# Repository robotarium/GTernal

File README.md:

# Setup Process for GTernal

# 1 - Repository Setup
During the setup process, each robot runs an automatic setup script which clones the firmware from a GitHub repository. By default, the setup script clones the official GTernal repository. This needs to be changed to clone your repository with updated configuration files. If you are not familiar with Git or GitHub, please refer to here: https://docs.github.com/en/get-started/quickstart/fork-a-repo

1. Fork this GTernal repository.
2. Clone the forked repository to your computer.
3. Update 'GTernal/config/env_variables.sh'
4. Push the change to your repository.

# 2 - Program Teensy
1. Install Teensyduino (https://www.pjrc.com/teensy/td_download.html)
2. Copy and paste all library folders in `GTernal/firmware/Teensy/libraries` to `Arduino/libraries`.
> [!NOTE]
> The absolute path for the `Arduino/libraries` directory is OS dependent, and this can be found here: https://support.arduino.cc/hc/en-us/articles/4412950938514-Open-the-Sketchbook
    
> [!NOTE]
> The firmware for Teensy requires ArduinoJson 5.13 which is included in `GTernal/firmware/Teensy/libraries`.
> ArduinoJson 6 is currently not compatible with the firmware.
3. Connect a Teensy to the computer using a micro-USB cable.
> [!NOTE]
> The micro-USB cable needs to be directly connected to the Teensy and not the micro-USB port on the robot PCB.
4. Run Teensyduino and open `defaultOperation.ino` located in `GTernal/firmware/defaultOperation` directory.
5. Select the Teensy board to be flashed under `Tools > Port`
6. Click the upload icon (right arrow icon).

# 3 - Make the Base Image for Raspberry Pi
## 1 - Install Raspberry Pi OS on an SD Card
1. Install and run the Raspberry Pi Imager (https://www.raspberrypi.com/software/). The instuction is for Raspberry Pi Imager v.1.8.5
2. For 'Raspberry Pi Device,' select the version of the Pi used.
3. For 'Operating System,' select `Raspberry Pi OS (other)` and select `Raspberry Pi OS (Legacy, 64-bit) Lite`. For Raspberry Pi Zero 1s, select `Raspberry Pi OS (Legacy, 32-bit) Lite`.
4. For 'Storage,' choose the micro-SD card to be used.
5. Click 'NEXT' and 'EDIT SETTINGS.'
6. Under 'GENERAL' tab, check 'Set username and password' and type `pi` for the 'Username' and `raspberry` for 'Password.'
7. Next, check 'Configure wireless LAN' and enter 'SSID' and 'Password' for the router.
8. Change 'Wireless LAN country' to 'US.' 'Set locale settings' is optional.
9. Under 'SERVICES' tab, check 'Enable SSH' and 'Use password authentication'
10. Click 'SAVE' and click 'YES.'
> [!NOTE]
> Whenever the Raspberry Pi Imager is restarted, make sure to re-type the passwords for the Pi and the Wifi. The Raspberry Pi Imager seems to be ruining the passwords saved in the advanced setting when the program is restarted even if the 'Image customization options' is set to 'to always use.'

## 2 - Setup the Base Image
1. Insert the SD card from the previous step into a Raspberry Pi and power it on. It should automatically connect to the wifi specified in Step 2.1.7. The Pi needs some time to boot for the first time.
2. Identify the MAC address of the Raspberry Pi. On a Linux comptuer, this can be done by running
    ```
    sudo arp-scan -I <network-device-name> -l -t 100 -r 5
    ```
    Alternatively, you can navigate to the router settings page (typically '192.168.1.1' or '10.0.0.1') using a web browser. The new Pi will appear as 'RASPBERRYPI.'
3. Add the MAC address to 'path-to-parent-directory/GTernal/config/mac_list.json' file as
    ```
    "<MAC-address-of-Pi>":"base_image"
    ```
    e.g., `{
            "d8:3a:dd:bc:0c:3c":"base_image"
           }`
4. On your computer, run
    ```
    cd <path-to-parent-directory>/GTernal/interfacing
    ./setup.sh setup_base_image
    ```
    When prompted for password, enter the password of your computer. When prompted 'Enter secrets for robots,' enter the password for the Raspberry Pis, `raspberry`.
    This will automatically setup the SD card as the base image. Wait for 'DONE SETTING UP BASE IMAGE' message on the terminal.
5. In case of using another network for the robot for actual deployment, edit the wireless LAN credentials.
    First, ssh into the robot.
    ```
    ssh pi@<ip-address-of-robot>
    ```
    Then, edit the wpa_supplicant.conf file to update the wireless LAN credentials.
    ```
    sudo nano /etc/wpa_supplicant/wpa_supplicant.conf
    ```

6. (Optional) Pull the base firmware image to reduce the setup time.
    - If the wireless LAN credential has changed in the previous step, restart the Raspberry Pi.<br>
        ```
         ssh pi@<ip-address-of-robot>
         sudo reboot
        ```
    - Follow the instructions in Section 4 up to 4.1.2.<br>
    - Next, ssh into the robot.
        ```
        ssh pi@<ip-address-of-robot>
        ```
    - Run
        ```
        cd <path-to-parent-directory>/GTernal/docker/base_image/
        ./docker_pull.sh
        ```

5. On the ssh terminal, shutdown the Pi by running
    ```
    sudo reboot
    ```
6. Remove the SD card from the Pi and insert it to your computer.
7. On your computer, identify the name of the SD card by running
    ```
    sudo fdisk -l
    ```
    The device name will be something like '/dev/sdb'. Look for the device with the storage size that matches the capacity of the SD card.
> [!NOTE]
> You must enter the device name without any numbers. For example, if you see '/dev/sdb1' and '/dev/sdb2', the device name is `/dev/sdb`.
8. Create the image of the SD card on your computer by running
    ```
    sudo dd if=<name-of-the-sd-card> of=<desired-directory>/GTernal_base_image.img bs=4M status=progress
    ```
    e.g., `sudo dd if=/dev/sdb of=~/GTernal_base_image.img bs=4M status=progress`<br>
9. Shrink the size of the base image by running
    ```
    wget https://raw.githubusercontent.com/Drewsif/PiShrink/master/pishrink.sh

    chmod +x ./pishrink.sh

    sudo ./pishrink.sh <path-to-the-base-image>/GTernal_base_image.img
    ```
    e.g., `sudo ./pishrink.sh ~/GTernal_base_image.img`

## 3 - Clone the Base Image
1. Insert a new SD card into your computer to load the base image.
2. Identify the name of the SD card by running
    ```
    sudo fdisk -l
    ```
3. Run
    ```
    sudo mount | grep <device-name>
    ```
    e.g. `sudo mount | grep /dev/sdb`
    to check if any of the partitions of the SD card is mounted.<br>
    If the output is not blank, run
    ```
    sudo umount <device-name1> <device-name2> ... <device-nameN>
    ```
    e.g. `sudo umount /dev/sdb1 /dev/sdb2`<br>
    to unmount all listed partitions of the device.
4. Load the SD card with the base image by running
    ```
    sudo dd if=<path-to-the-base-image>/GTernal_base_image.img of=<name-of-the-sd-card> status=progress
    ```
    e.g., `sudo dd if=~/GTernal_base_image.img of=/dev/sdb bs=4M status=progress`<br>
> [!NOTE]
> The status message may stop updating at some point. Please continue waiting for the write process to finish.
5. Load as many SD cards as needed with the base image. More detailed instructions on cloning an SD card image can be found here: https://beebom.com/how-clone-raspberry-pi-sd-card-windows-linux-macos/

# 4 - Load the Raspberry Pi with the Default firmware
This section assumes that:
1. You have micro-SD cards loaded as detailed in the previous section.
2. You have fully assembled robots.
> [!NOTE]
> Check if the Pi and Teensy are connected through UART. If the Pi is not connected with a programmed Teensy as instructed in Step 1, the firmware will not be started by the setup script properly in the following steps.
3. Only the new robots to be setup are connected to the WiFi.
> [!WARNING]
> The current automatic setup script looks for all robots with the MAC addresses specified in 'GTernal/config/mac_list.json' file and starts the setup process for the robots. Therefore, it will start the setup process even for the robots already with the firmware installed if they are connected to the WiFi. Since this may cause problems for the existing robots, it is advised to only turn on the new robots to be set up.

## 1 - Firmware Docker Image Setup
The "docker_run.sh" script makes each robot pull the firmware image from either Docker Hub of a local Docker registry instead of building the firmware docker image directly on each robot. This saves a lot of time when building multiple robots. Also, with "v2tec/watchtower" image running on the robots, each robot downloads and runs the newest firmware image uploaded to the Docker Hub automatically. Therefore, it is unnecessary to manually update the firmware of each robot when a new firmware image is built and pushed to Docker Hub/local Docker registry.

### 1 - Build the Base Firmware Image
1. Inspect and update the environment variables in `config/env_variables.sh`
2. Build the base image
    ```
    cd <path-to-parent-directory>/GTernal/docker/base_image/
    ./docker_build.sh
    ```

### 2 - Tag the Base Image and Push it to a Docker Registry

#### 2.1 - Docker Hub (Online)
1. Log into the Docker Hub with
    ```
    docker login
    ```
2. Run
    ```
    cd <path-to-parent-directory>/GTernal/docker/base_image/
    ./docker_push.sh
    ```

#### 2.2 - Local Docker registry (Local)
1. Start a local Docker registry
    ```
    cd <path-to-parent-directory>/GTernal/docker/
    ./docker_registry.sh
    ```
2. Run
    ```
    cd <path-to-parent-directory>/GTernal/docker/base_image/
    ./docker_push_local.sh
    ```

### 3 - Build the Firmware Image
1. Build the firmware image
    ```
    cd <path-to-parent-directory>/GTernal/docker/
    ./docker_build.sh
    ```

### 4 - Tag the Firmware Image and Push it to a Docker Registry

#### 4.1 - Docker Hub (Online)
1. Run
    ```
    cd <path-to-parent-directory>/GTernal/docker/
    ./docker_push.sh
    ```

#### 4.2 - Local Docker registry (Local)
1. Run
    ```
    cd <path-to-parent-directory>/GTernal/docker/
    ./docker_push_local.sh
    ```

## 2 - Robot Setup
<!-- > [!IMPORTANT]
> It is recommended to only turn on the new robots to be set up. The current automatic setup script looks for all robots with the MAC addresses specified in 'GTernal/config/mac_list.json' file and starts the setup process for the robots. Therefore, it will start the setup process even for the robots already with the firmware installed if they are connected to the WiFi. Since this may cause problems for the existing robots, it is recommended to only turn on the new robots that need to be set up. -->
1. Insert the loaded micro-SD cards to the robots' Raspberry Pis and power the robots up using the switch on each PCB. They should automatically connect to the wifi specified in Step 3.7.

2. On your computer, check if all the Raspberry Pis are connected to the WiFi router by running
    ```
    sudo arp-scan -I <network-device-name> -l -t 100 -r 5
    ```
    e.g., `sudo arp-scan -I enp4s0 -l -t 100 -r 5`

    Check if the number of Raspberry Pis found by the above command matches the total number of Raspberry Pis being set up. Wait a few more minutes and check again if not all Pis show up in the list.

> [!NOTE]
> The \<network-device-name\> can be found by running 'ifconfig' command into the terminal. There may be multiple network devices on your computer. The right device is the one connected to the same WiFi network as the Raspberry Pis. Typically, the local IP address assigned by a network router is '192.168.x.x' or '10.0.x.x.'

3. Assign an unallocated robot ID# for the MAC address of a Raspberry Pi found in the previous step. Then, add/replace the robot ID# and the MAC address of the Raspberry Pi in 'GTernal/config/mac_list.json'

> [!NOTE]
> When assigning an index to a new robot, assign an Aruco tag ID or the ID engraved on a Vicon hat plate. Make sure not to use any numbers that are already assigned to other robots. The lasercutting design files for the Vicon hats can be found in `GTernal/GTernal_design_files`

<!-- 4. Replace lines 12 and 13 in 'GTernal/docker/docker_run.sh' with the IP address and port of the MQTT host.

   > [!NOTE]
   > The default GTernal firmware requires an MQTT broker. For more information about the MQTT broker, please refer to https://github.com/robotarium/mqtt_broker. -->

4. Start the setup process by running
    ```
    cd path-to-parent-directory/GTernal/interfacing
    ./setup.sh setup_from_base <#-of-robots-being-set-up>
    ```
    e.g., `./setup.sh setup_from_base 10`

    When prompted 'Enter secrets for robots,' enter the password for the Raspberry Pis, 'raspberry'

> [!NOTE]
> The config/mac_list.json file of the robots will be updated to the config/mac_list.json file on your computer via SCP.

<!-- 5. Update the 'mac_list.json' file on the robots by running
```
cd path-to-parent-directory/GTernal/interfacing
./update_mac.sh <#-of-robots-being-set-up>
```
e.g. ./update_mac.sh 10

When prompted 'Enter secrets for robots,' enter the password for the Raspberry Pis, 'raspberry'

The Raspberry Pis will reboot after updating 'mac_list.json' file. -->

<!-- ## 2 - Network Host Name Change (Optional)
This process changes the name of the Raspberry Pi on the network. This helps to identify each robot easily on the router page ('192.168.1.1' or '10.0.0.1'). See Step 2.2, if you forgot how to access the router page.

After the setup process is completed,
Run
```
sudo raspi-config nonint do_hostname <hostname>
```
on the Raspberry Pi, and change the Host Name to 'robot#' where # is the new robot index assigned to the Pi in Step 3.

Reboot the Pi to apply the new network host name by selecting 'yes' when the raspi-config asks for a restart, or by using
```
sudo reboot
``` -->

<!-- ## 2 - Manual Installation

This section details the manual installation process for the firmware. This process is unnecessary if the automatic setup in the previous section is performed.

### 1 Remove Unused Services

Remove plymouth with 

```
sudo apt-get purge --remove plymouth
```

Disable unused services with 

```
sudo systemctl disable triggerhappy.service
sudo systemctl disable hciuart.service
sudo systemctl disable keyboard-setup.service
sudo systemctl disable dphys-swapfile.service
```

### 2 - Install Docker

This section follows from the official (Docker)[https://docs.docker.com/install/linux/docker-ce/ubuntu/].  First, remove old versions of Docker.

```
sudo apt-get remove docker docker-engine docker.io
```

Next, install Docker using the convenience script.

```
curl -fsSL get.docker.com -o get-docker.sh && export VERSION=23.0 && sh get-docker.sh
```

Now tie Docker to the pi user so that we don't need sudo to use Docker.

```
sudo usermod -aG docker pi
```

### 3 - Clone Git Repos and install Deps

Install pip for python3

```
sudo apt-get install python3-pip
```

To clone the firmware, run
```
sudo apt-get install git
git clone https://github.com/robotarium/gritsbot_2
```

Also, install the MAC discovery repository
```
git clone https://github.com/robotarium/mac_discovery
```

as well as the python serial library used to communicate to the robot.

```
python3 -m pip install pyserial
```

### 4 - WiFi Power Management

Turn off power management by adding the line
```
/sbin/iw dev wlan0 set power_save off
```

in the file /etc/rc.local.  This line disables WiFi power management on boot.

### 5 - Start necessary containers

From wherever the git repository is cloned, run 
```
cd <path_to_gritsbot_2_repo>/docker
./docker_run.sh
./docker_watch.sh
```
which will permanently start a Docker container running the firmware and the watchtower container.  Watchtower watches containers and automatically updates them from Dockerhub.  This watchtower instance
checks and updates **all running containers**, so this instance will also update the MAC container as well.

Start MAC discovery as well with
```
cd <path_to_mac_discovery_repo>/docker
./docker_run.sh
``` -->

# 5 - Test Robots
1. Clone the mqtt_broker repo
    ```
    git clone https://github.com/robotarium/mqtt_broker.git
    ```
2. Run the MQTT broker Docker container
    ```
    cd <path-to-parent-directory>/mqtt_broker/docker/
    ./docker_run.sh <ip-address-of-your-computer>
    ```
3. Clone the vizier repository with
    ```
    git clone https://github.com/robotarium/vizier.git
    ```

4. Install vizier with
    ```
    cd path-to-parent-directory/vizier
    python3 -m pip install .
    ```

5. Check the status of a robot with
    ```
    python3 -m vizier.vizier --host <ip-address-of-MQTT-host> --get <robot#>/status
    ```
    e.g., `python3 -m vizier.vizier --host 192.168.1.8 --get 21/status`

6. Send a motor command to a robot with
    ```
    python3 -m vizier.vizier --host <ip-address-of-MQTT-host> --publish matlab_api/<robot#> '{"v":1.0,"w":0.0}'
    ```
    e.g., `python3 -m vizier.vizier --host 192.168.1.8 --publish matlab_api/21 '{"v":1.0,"w":0.0}'`

    "v" and "w" are the desired linear and angular velocity of the robot, respectively. With this command, the robot will stop after 1 second for safety purposes.

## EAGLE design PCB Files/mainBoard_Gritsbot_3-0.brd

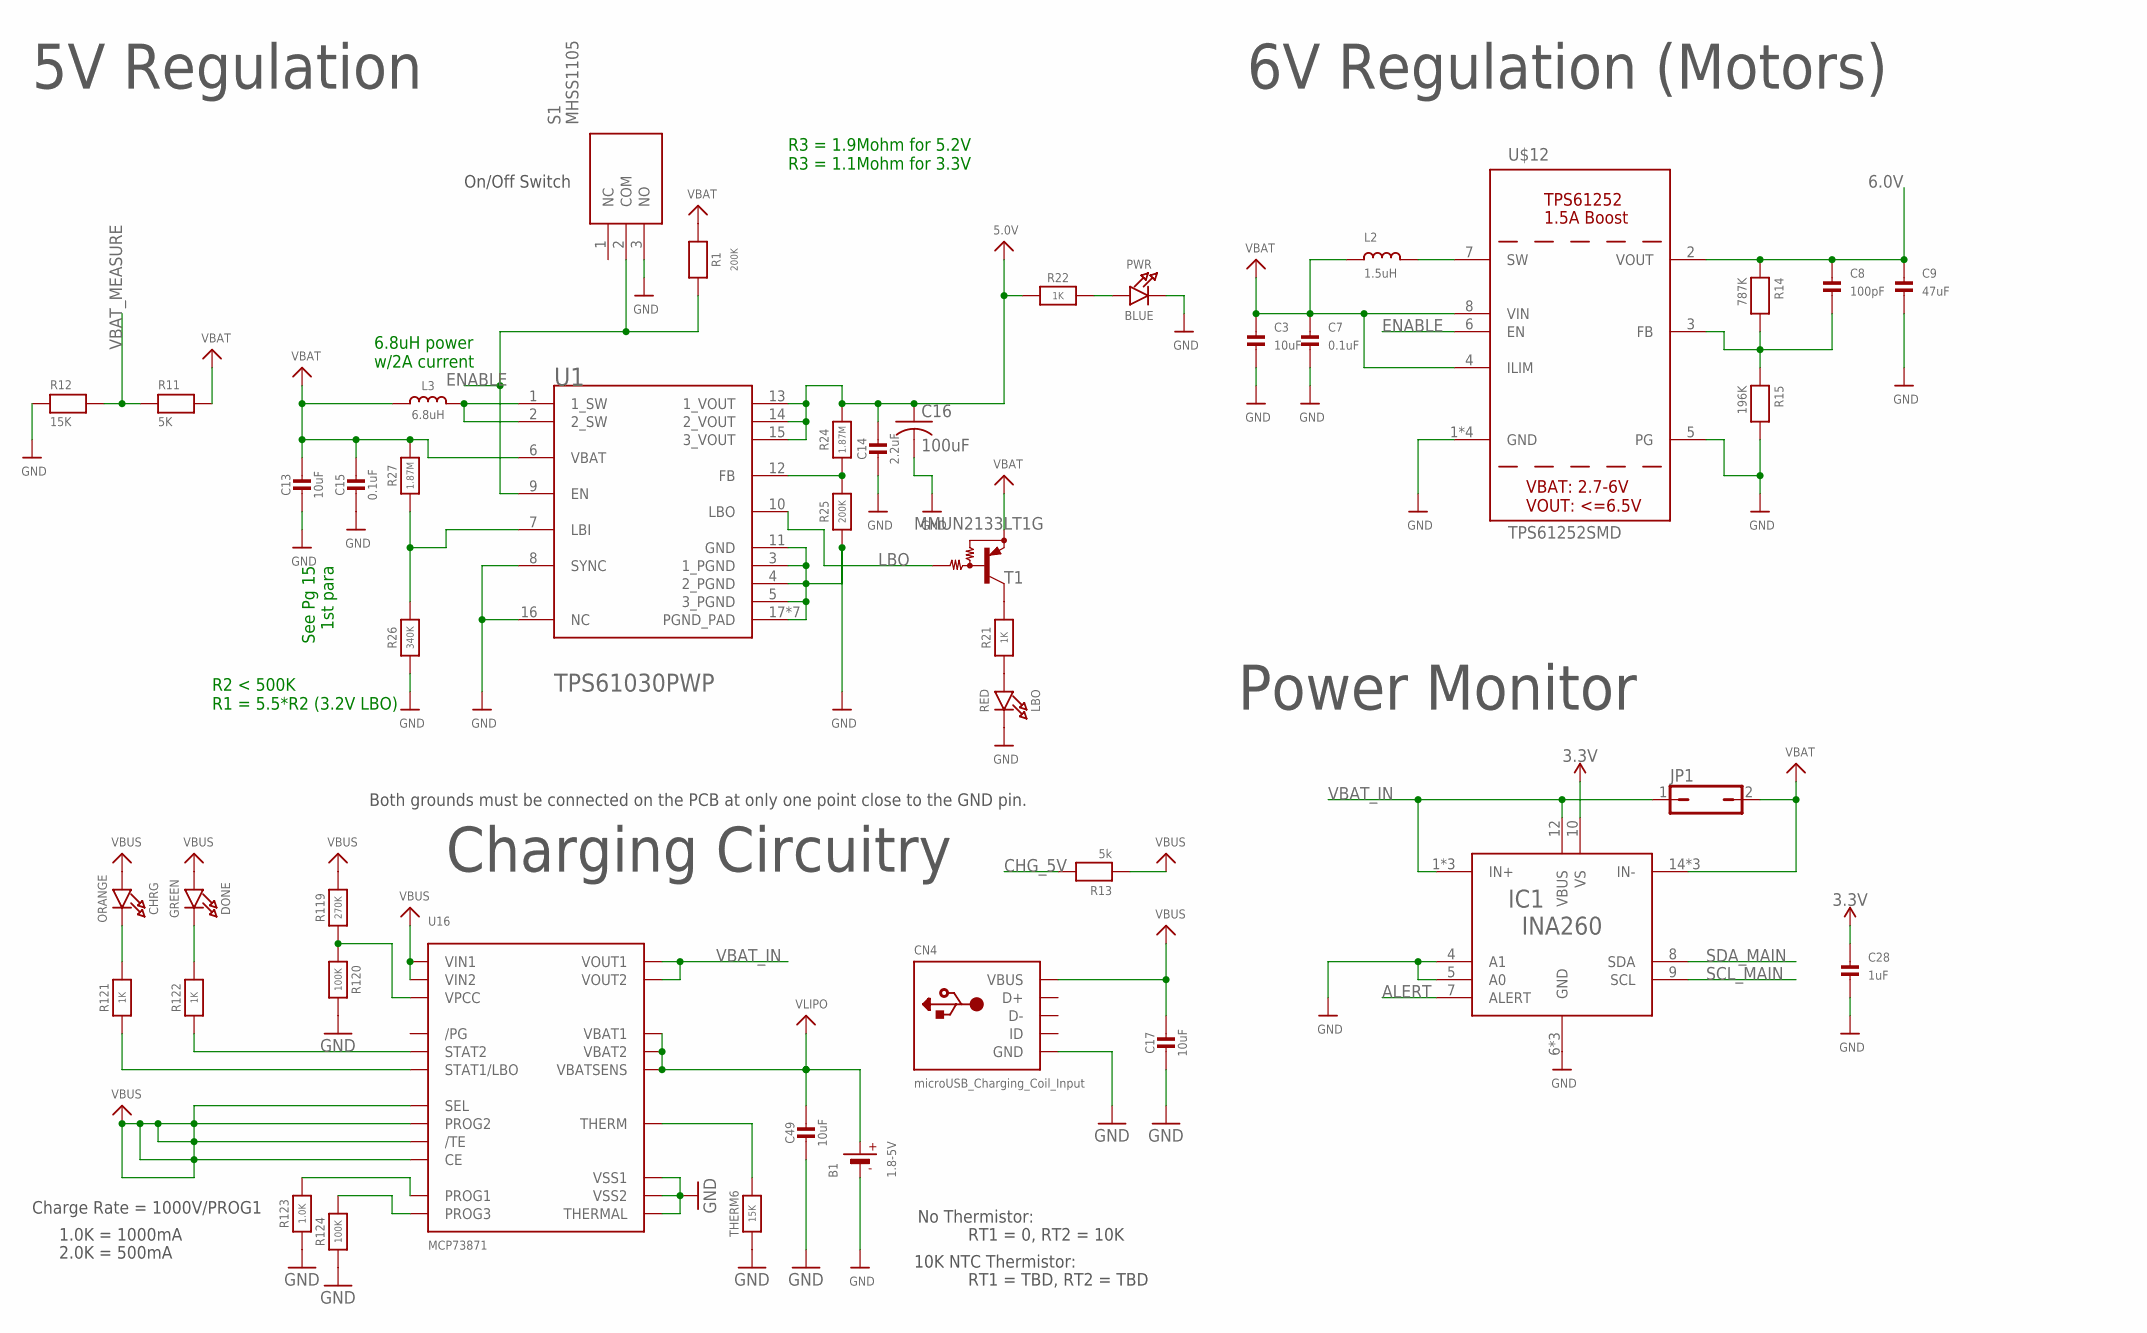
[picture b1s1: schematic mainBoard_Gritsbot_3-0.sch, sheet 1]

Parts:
B1: 1.8-5V; JSTPH2
C3: 10uF; 0603
C7: 0.1uF; 0805
C8: 100pF; 0603
C9: 47uF; 1206
C13, C17, C49: 10uF; 0805-NO
C14: 2.2uF; 0805-NO
C15: 0.1uF; 0805_10MGAP
C16: 100uF; C1210
C28: 1uF; 0603-NO
CHRG: ORANGE; CHIPLED_0805_NOOUTLINE
CN4: microUSB_Charging_Coil_Input; 4UCONN_20329
DONE: GREEN; CHIPLED_0805_NOOUTLINE
IC1: INA260; TSSOP16
JP1: JP1Q; JP1
L2: 1.5uH; MURATA_DFE252012P-1R5M=P2
L3: 6.8uH; INDUCTOR_5X5MM_TDK_VLC5045
LBO: RED; CHIPLED_0805_NOOUTLINE
PWR: BLUE; CHIPLED_0805_NOOUTLINE
R1, R25: 200K; 0805-NO
R11: 5K; 0805
R12: 15K; 0805
R13: 5k; 0805
R14: 787K; 0805
R15: 196K; 0805
R21, R22, R121, R122: 1K; 0805-NO
R24: 1.87M; 0805-NO
R26: 340K; _0805MP
R27: 1.87M; _0805MP
R119: 270K; 0805-NO
R120, R124: 100K; 0805-NO
R123: 1.0K; 0805-NO
S1: MHSS1105
T1: MMUN2133LT1G; SC59-BEC
THERM6: 15K; 0805-NO
U1: TEXAS_INSTRUMENTS_TPS61030PWPTEXAS_INSTRUMENTS_TP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; TEXAS_INSTRUMENTS_TPS61030PWP_0
U16: MCP73871; QFN20_4MM
U$12: TPS61252SMD; TPS61252

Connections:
3.3V: C28.1, IC1.10 (VS); also elsewhere on the board
5.0V: C14.1, C16.1, R22.1, R24.2, U1.13 (1_VOUT), U1.14 (2_VOUT), U1.15 (3_VOUT); also elsewhere on the board
6.0V: C8.1, C9.1, R14.1, U$12.2 (VOUT); also elsewhere on the board
ALERT: IC1.7 (ALERT)
CHG_5V: R13.2; also elsewhere on the board
ENABLE: R1.2, S1.2 (COM), U1.9 (EN), U$12.6 (EN)
GND: B1.1 (-), C3.2, C7.2, C9.2, C13.2, C14.2, C15.2, C16.2, C17.2, C28.2, C49.2, CN4.BASE@1 (GND), CN4.BASE@2 (GND), CN4.GND, CN4.SPRT@1 (GND), CN4.SPRT@2 (GND), CN4.SPRT@3 (GND), CN4.SPRT@4 (GND), IC1.4 (A1), IC1.5 (A0), IC1.6 (GND), IC1.11 (GND), IC1.13 (GND), LBO.C, PWR.C, R12.1, R15.2, R25.1, R26.1, R120.2, R123.1, R124.1, S1.3 (NO), THERM6.1, U1.3 (1_PGND), U1.4 (2_PGND), U1.5 (3_PGND), U1.8 (SYNC), U1.11 (GND), U1.16 (NC), U1.17 (PGND_PAD), U1.PAD_1 (PGND_PAD), U1.PAD_2 (PGND_PAD), U1.PAD_3 (PGND_PAD), U1.PAD_4 (PGND_PAD), U1.PAD_5 (PGND_PAD), U1.PAD_6 (PGND_PAD), U16.P$10 (VSS1), U16.P$11 (VSS2), U16.P$21 (THERMAL), U$12.1 (GND), U$12.5 (PG), U$12.P$2_GND (GND), U$12.P$3_GND (GND), U$12.THERMAL_GND (GND); also elsewhere on the board
LBO: T1.B, U1.10 (LBO)
unnamed: R24.1, R25.2, U1.12 (FB)
unnamed: L2.P$2 (2), U$12.7 (SW)
unnamed: C8.2, R14.2, R15.1, U$12.3 (FB)
unnamed: L3.P$2 (2), U1.1 (1_SW), U1.2 (2_SW)
unnamed: R26.2, R27.1, U1.7 (LBI)
unnamed: LBO.A, R21.1
unnamed: R21.2, T1.C
unnamed: PWR.A, R22.2
unnamed: R119.1, R120.1, U16.P$2 (VPCC)
unnamed: R122.1, U16.P$7 (STAT2)
unnamed: R121.1, U16.P$8 (STAT1/LBO)
unnamed: R123.2, U16.P$13 (PROG1)
unnamed: THERM6.2, U16.P$5 (THERM)
unnamed: DONE.C, R122.2
unnamed: CHRG.C, R121.2
unnamed: R124.2, U16.P$12 (PROG3)
SCL_MAIN: IC1.9 (SCL); also elsewhere on the board
SDA_MAIN: IC1.8 (SDA); also elsewhere on the board
VBAT: C3.1, C7.1, C13.1, C15.1, IC1.14 (IN-), IC1.15 (IN-), IC1.16 (IN-), JP1.2, L2.P$1 (1), L3.P$1 (1), R1.1, R11.2, R27.2, T1.E, U1.6 (VBAT), U$12.4 (ILIM), U$12.8 (VIN)
VBAT_IN: IC1.1 (IN+), IC1.2 (IN+), IC1.3 (IN+), IC1.12 (VBUS), JP1.1, U16.P$1 (VOUT1), U16.P$20 (VOUT2)
VBAT_MEASURE: R11.1, R12.2; also elsewhere on the board
VBUS: C17.1, CHRG.A, CN4.VBUS, DONE.A, R13.1, R119.2, U16.P$3 (SEL), U16.P$4 (PROG2), U16.P$9 (/TE), U16.P$17 (CE), U16.P$18 (VIN1), U16.P$19 (VIN2)
VLIPO: B1.2 (+), C49.1, U16.P$14 (VBAT1), U16.P$15 (VBAT2), U16.P$16 (VBATSENS)

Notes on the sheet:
R2 < 500K R1 = 5.5*R2 (3.2V LBO)
Charging Circuitry
5V Regulation
6V Regulation (Motors)
Charge Rate = 1000V/PROG1
1.0K = 1000mA
2.0K = 500mA
No Thermistor:
10K NTC Thermistor:
RT1 = 0, RT2 = 10K
RT1 = TBD, RT2 = TBD
Both grounds must be connected on the PCB at only one point close to the GND pin.
On/Off Switch
See Pg 15 1st para
6.8uH power w/2A current
R3 = 1.9Mohm for 5.2V R3 = 1.1Mohm for 3.3V
Power Monitor

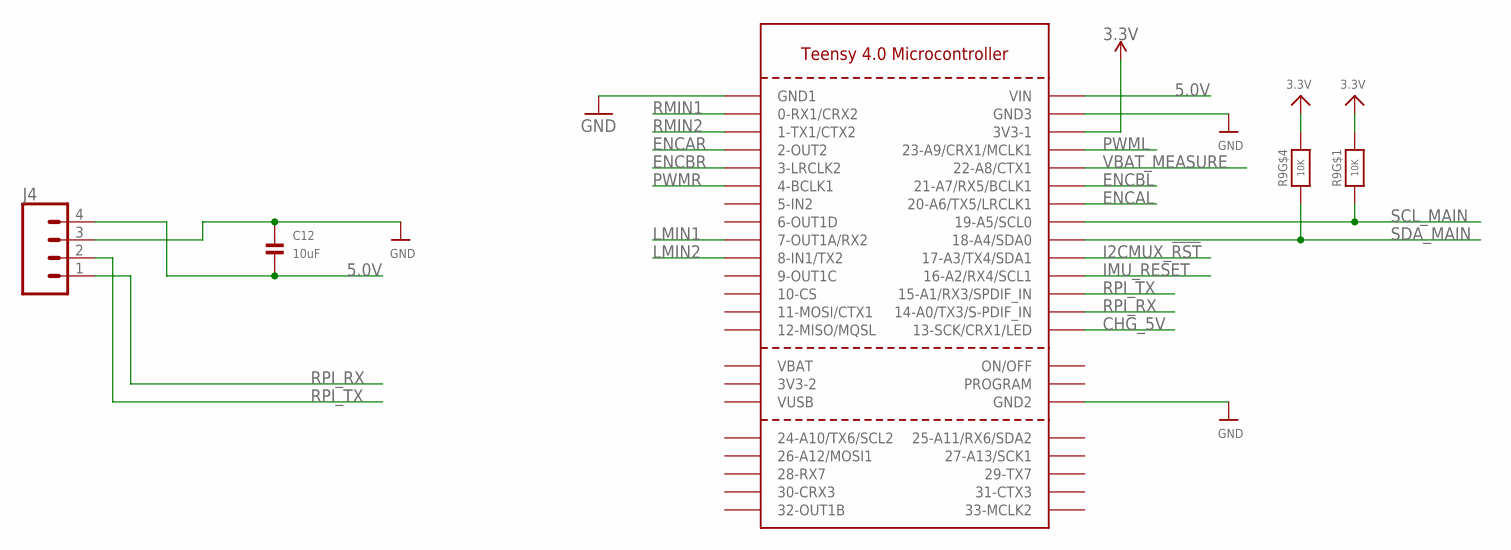
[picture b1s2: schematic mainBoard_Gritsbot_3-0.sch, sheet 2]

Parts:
C12: 10uF; 0603
J4: CONN_041X04_NO_SILK; 1X04_NO_SILK
R9: 10K; RESPACK_4X0603
U$57: TEENSY40

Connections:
3.3V: R9.1, R9.4 (1), U$57.3V3-1; also elsewhere on the board
5.0V: C12.2, J4.4, U$57.VIN; also elsewhere on the board
CHG_5V: U$57.13-SCK/CRX1/LED; also elsewhere on the board
ENCAL: U$57.20-A6/TX5/LRCLK1; also elsewhere on the board
ENCAR: U$57.2-OUT2; also elsewhere on the board
ENCBL: U$57.21-A7/RX5/BCLK1; also elsewhere on the board
ENCBR: U$57.3-LRCLK2; also elsewhere on the board
GND: C12.1, J4.3, U$57.GND1, U$57.GND2, U$57.GND3; also elsewhere on the board
I2CMUX_!RST: U$57.17-A3/TX4/SDA1; also elsewhere on the board
IMU_RESET: U$57.16-A2/RX4/SCL1; also elsewhere on the board
LMIN1: U$57.7-RX2/OUT1A (7-OUT1A/RX2); also elsewhere on the board
LMIN2: U$57.8-TX2/IN1 (8-IN1/TX2); also elsewhere on the board
PWML: U$57.23-A9/CRX1/CCLK1 (23-A9/CRX1/MCLK1); also elsewhere on the board
PWMR: U$57.4-BCLK2 (4-BCLK1); also elsewhere on the board
RMIN1: U$57.0-RX1 (0-RX1/CRX2); also elsewhere on the board
RMIN2: U$57.1-TX1 (1-TX1/CTX2); also elsewhere on the board
RPI_RX: J4.1, U$57.14-A0/TX3/S-PFI_OUT (14-A0/TX3/S-PDIF_IN)
RPI_TX: J4.2, U$57.15-A1/RX3/S-PDIF_IN (15-A1/RX3/SPDIF_IN)
SCL_MAIN: R9.8 (2), U$57.19-A5/SCL0; also elsewhere on the board
SDA_MAIN: R9.5 (2), U$57.18-A4/SDA0; also elsewhere on the board
VBAT_MEASURE: U$57.22-A8/CTX1; also elsewhere on the board

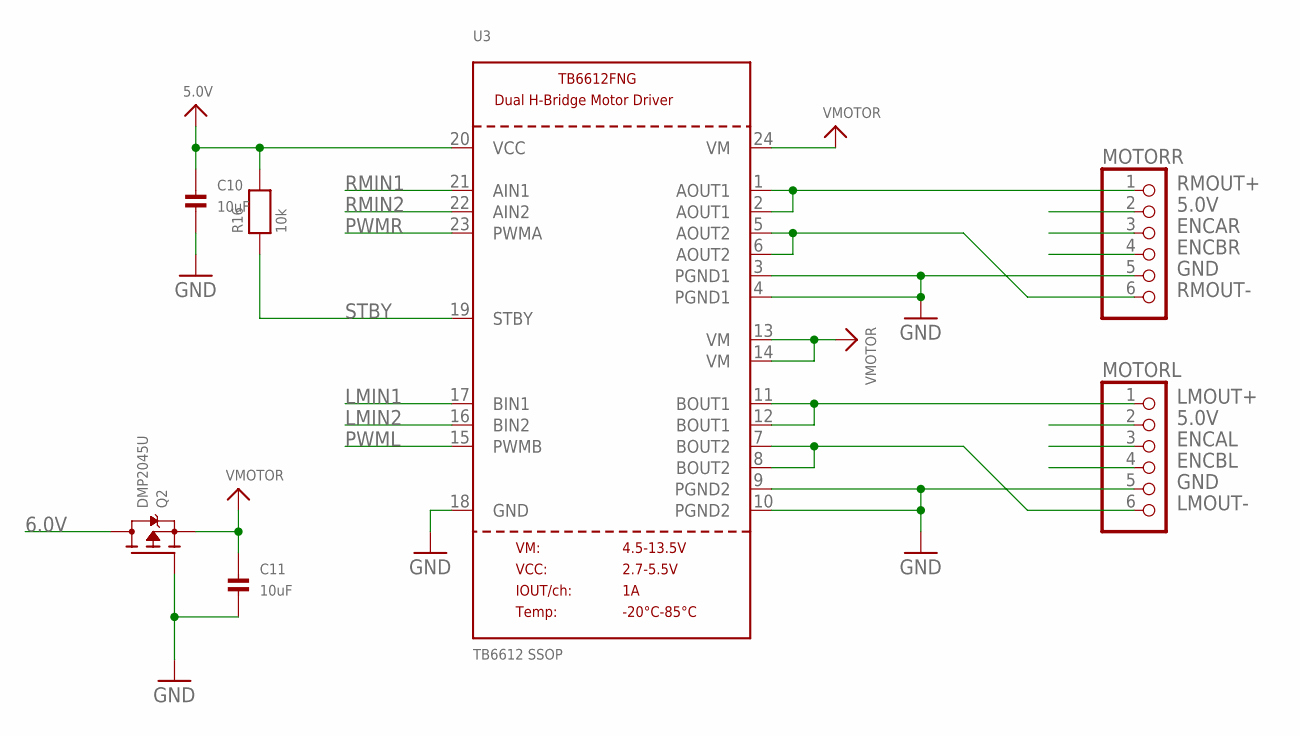
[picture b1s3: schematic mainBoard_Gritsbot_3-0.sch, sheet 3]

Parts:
C10, C11: 10uF; 0603
MOTORL: PINHD-1X6CB; 1X06-CLEANBIG
MOTORR: PINHD-1X6CB; 1X06-CLEANBIG
Q2: DMP2045U; SOT23-WIDE
R16: 10k; 0805
U3: TB6612 SSOP; SSOP24

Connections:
5.0V: C10.1, MOTORL.2, MOTORR.2, R16.2, U3.20 (VCC); also elsewhere on the board
6.0V: Q2.3 (D); also elsewhere on the board
ENCAL: MOTORL.3; also elsewhere on the board
ENCAR: MOTORR.3; also elsewhere on the board
ENCBL: MOTORL.4; also elsewhere on the board
ENCBR: MOTORR.4; also elsewhere on the board
GND: C10.2, C11.2, MOTORL.5, MOTORR.5, Q2.1 (G), U3.3 (PGND1), U3.4 (PGND1), U3.9 (PGND2), U3.10 (PGND2), U3.18 (GND); also elsewhere on the board
LMIN1: U3.17 (BIN1); also elsewhere on the board
LMIN2: U3.16 (BIN2); also elsewhere on the board
LMOUT+: MOTORL.1, U3.11 (BOUT1), U3.12 (BOUT1)
LMOUT-: MOTORL.6, U3.7 (BOUT2), U3.8 (BOUT2)
PWML: U3.15 (PWMB); also elsewhere on the board
PWMR: U3.23 (PWMA); also elsewhere on the board
RMIN1: U3.21 (AIN1); also elsewhere on the board
RMIN2: U3.22 (AIN2); also elsewhere on the board
RMOUT+: MOTORR.1, U3.1 (AOUT1), U3.2 (AOUT1)
RMOUT-: MOTORR.6, U3.5 (AOUT2), U3.6 (AOUT2)
STBY: R16.1, U3.19 (STBY)
VMOTOR: C11.1, Q2.2 (S), U3.13 (VM), U3.14 (VM), U3.24 (VM)

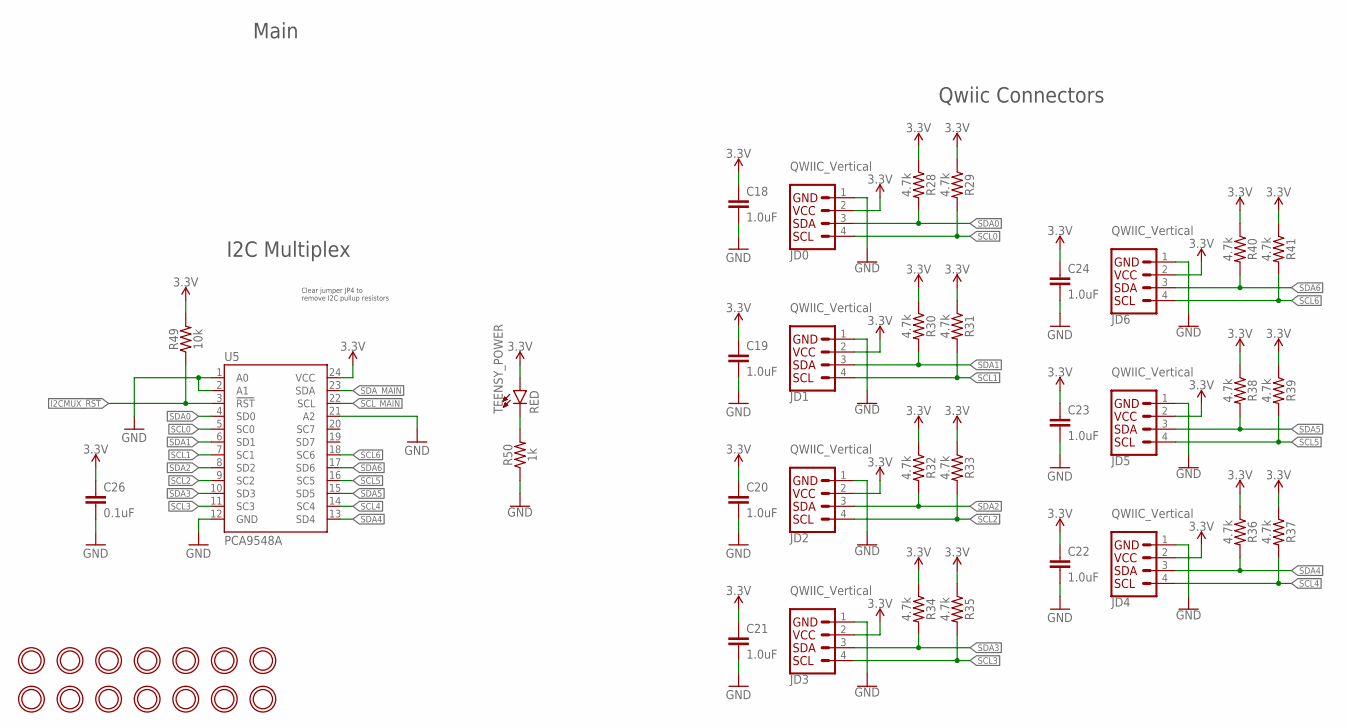
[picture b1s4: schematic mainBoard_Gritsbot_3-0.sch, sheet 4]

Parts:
C18, C19, C20, C21, C22, C23, C24: 1.0uF; 0603
C26: 0.1uF; 0603
JD0, JD1, JD2, JD3, JD4, JD5, JD6: QWIIC_Vertical; JST04_1MM_VERT
R28, R29, R30, R31, R32, R33, R34, R35, R36, R37, R38, R39, R40, R41: 4.7k; 0603
R49: 10k; 0603
R50: 1k; 0603
TEENSY_POWER: RED; LED-0603
U5: PCA9548A; TSSOP28
U$8, U$30, U$31, U$32, U$33, U$34, U$35, U$36, U$37, U$43, U$45, U$46, U$47, U$48: MOUNTINGHOLE2.5; MOUNTINGHOLE_2.5_PLATED

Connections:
3.3V: C18.1, C19.1, C20.1, C21.1, C22.1, C23.1, C24.1, C26.1, JD0.2, JD1.2, JD2.2, JD3.2, JD4.2, JD5.2, JD6.2, R28.1, R29.1, R30.1, R31.1, R32.1, R33.1, R34.1, R35.1, R36.1, R37.1, R38.1, R39.1, R40.1, R41.1, R49.2, TEENSY_POWER.A, U5.24 (VCC); also elsewhere on the board
GND: C18.2, C19.2, C20.2, C21.2, C22.2, C23.2, C24.2, C26.2, JD0.1, JD1.1, JD2.1, JD3.1, JD4.1, JD5.1, JD6.1, R50.1, U5.1 (A0), U5.2 (A1), U5.12 (GND), U5.21 (A2); also elsewhere on the board
I2CMUX_!RST: R49.1, U5.3 (!RST); also elsewhere on the board
unnamed: R50.2, TEENSY_POWER.C
SCL0: JD0.4, R29.2, U5.5 (SC0)
SCL1: JD1.4, R31.2, U5.7 (SC1)
SCL2: JD2.4, R33.2, U5.9 (SC2)
SCL3: JD3.4, R35.2, U5.11 (SC3)
SCL4: JD4.4, R37.2, U5.14 (SC4)
SCL5: JD5.4, R39.2, U5.16 (SC5)
SCL6: JD6.4, R41.2, U5.18 (SC6)
SCL_MAIN: U5.22 (SCL); also elsewhere on the board
SDA0: JD0.3, R28.2, U5.4 (SD0)
SDA1: JD1.3, R30.2, U5.6 (SD1)
SDA2: JD2.3, R32.2, U5.8 (SD2)
SDA3: JD3.3, R34.2, U5.10 (SD3)
SDA4: JD4.3, R36.2, U5.13 (SD4)
SDA5: JD5.3, R38.2, U5.15 (SD5)
SDA6: JD6.3, R40.2, U5.17 (SD6)
SDA_MAIN: U5.23 (SDA); also elsewhere on the board

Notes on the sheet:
Qwiic Connectors
Main
I2C Multiplex
Clear jumper JP4 to remove I2C pullup resistors

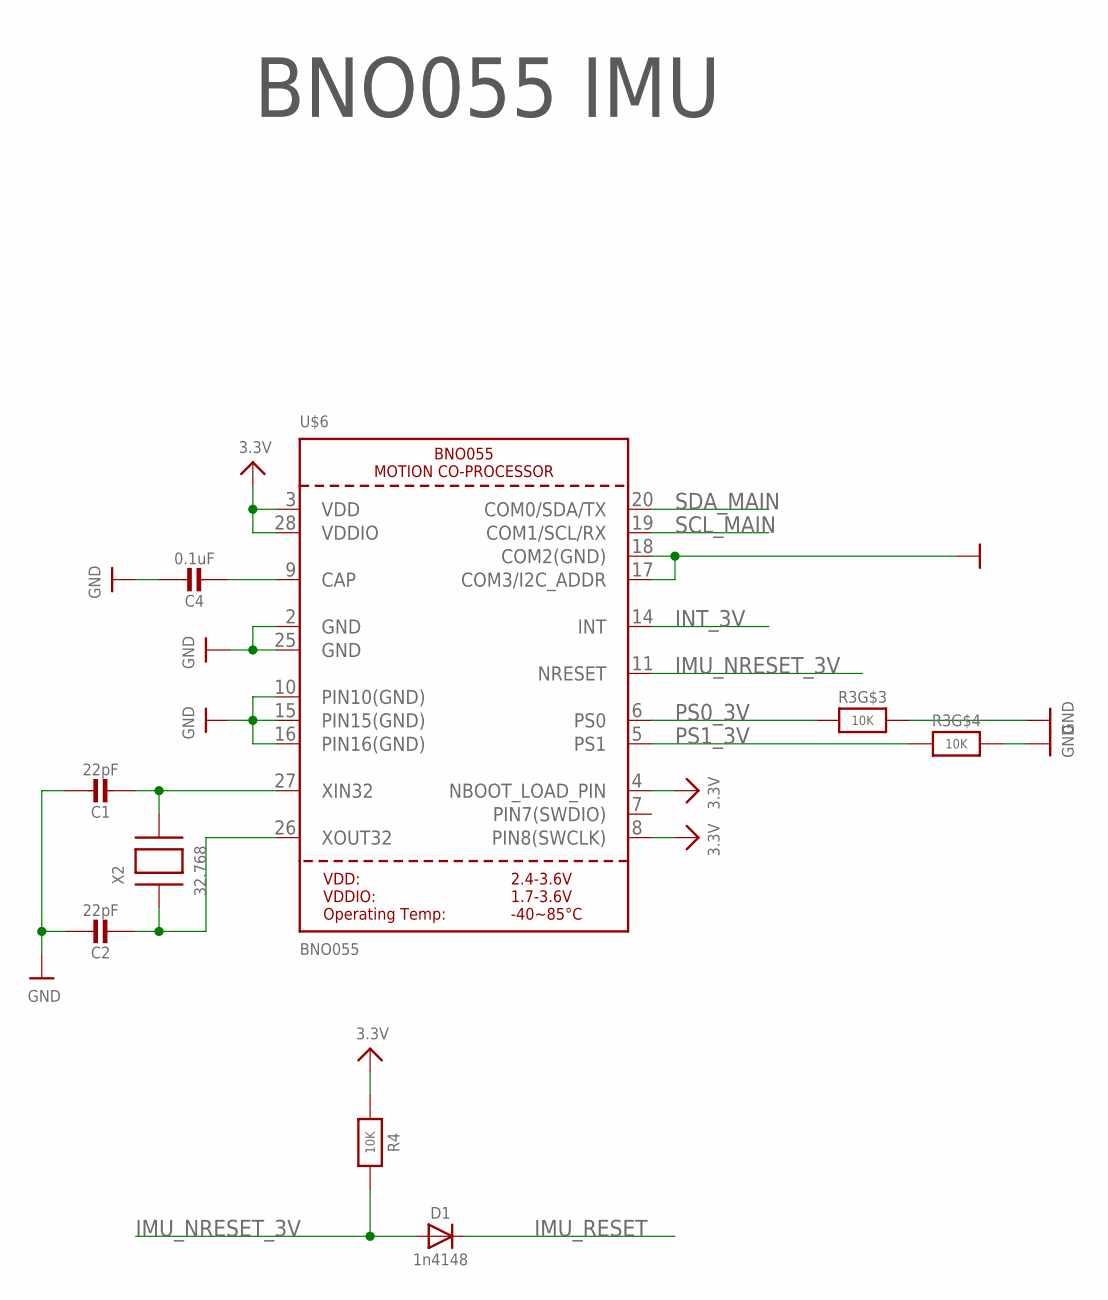
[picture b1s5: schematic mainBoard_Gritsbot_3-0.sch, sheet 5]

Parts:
C1, C2: 22pF; 0603-NO
C4: 0.1uF; 0603-NO
D1: 1n4148; SOD-323
R3: 10K; RESPACK_4X0603
R4: 10K; 0603-NO
U$6: BNO055
X2: 32.768; XTAL3215

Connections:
3.3V: R4.1, U$6.3 (VDD), U$6.4 (NBOOT_LOAD_PIN), U$6.8 (PIN8(SWCLK)), U$6.28 (VDDIO); also elsewhere on the board
GND: C1.1, C2.1, C4.1, R3.5 (2), R3.6 (2), U$6.2 (GND), U$6.10 (PIN10(GND)), U$6.15 (PIN15(GND)), U$6.16 (PIN16(GND)), U$6.17 (COM3/I2C_ADDR), U$6.18 (COM2(GND)), U$6.25 (GND); also elsewhere on the board
IMU_NRESET_3V: D1.A, R4.2, U$6.11 (NRESET)
IMU_RESET: D1.C; also elsewhere on the board
INT_3V: U$6.14 (INT)
unnamed: C1.2, U$6.27 (XIN32), X2.P$2
unnamed: C2.2, U$6.26 (XOUT32), X2.P$1
unnamed: C4.2, U$6.9 (CAP)
PS0_3V: R3.3 (1), U$6.6 (PS0)
PS1_3V: R3.4 (1), U$6.5 (PS1)
SCL_MAIN: U$6.19 (COM1/SCL/RX); also elsewhere on the board
SDA_MAIN: U$6.20 (COM0/SDA/TX); also elsewhere on the board

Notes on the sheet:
BNO055 IMU

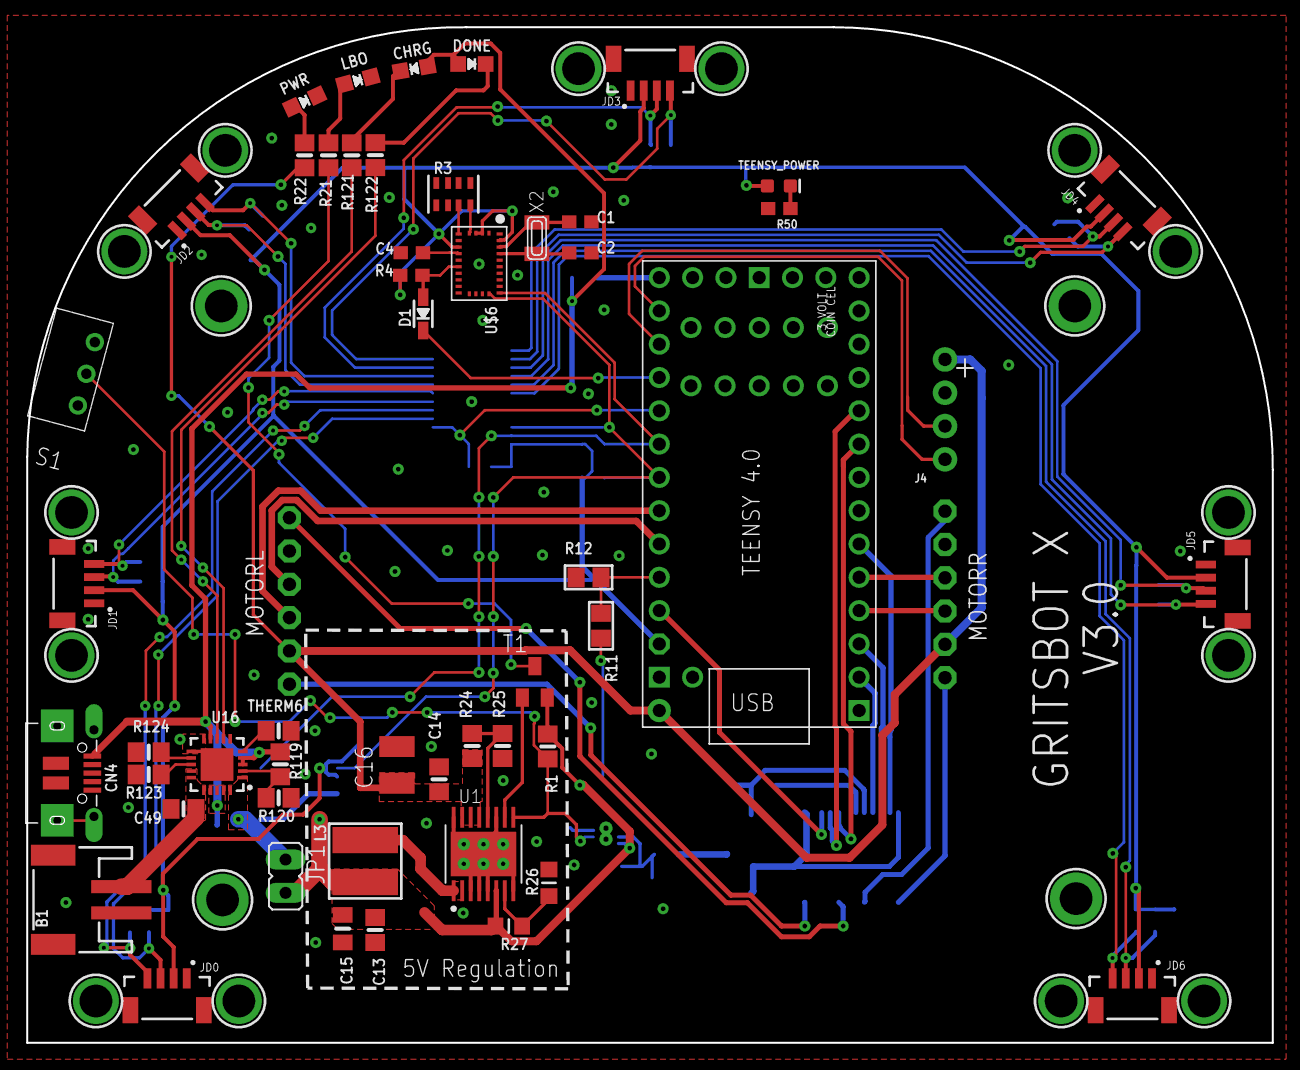
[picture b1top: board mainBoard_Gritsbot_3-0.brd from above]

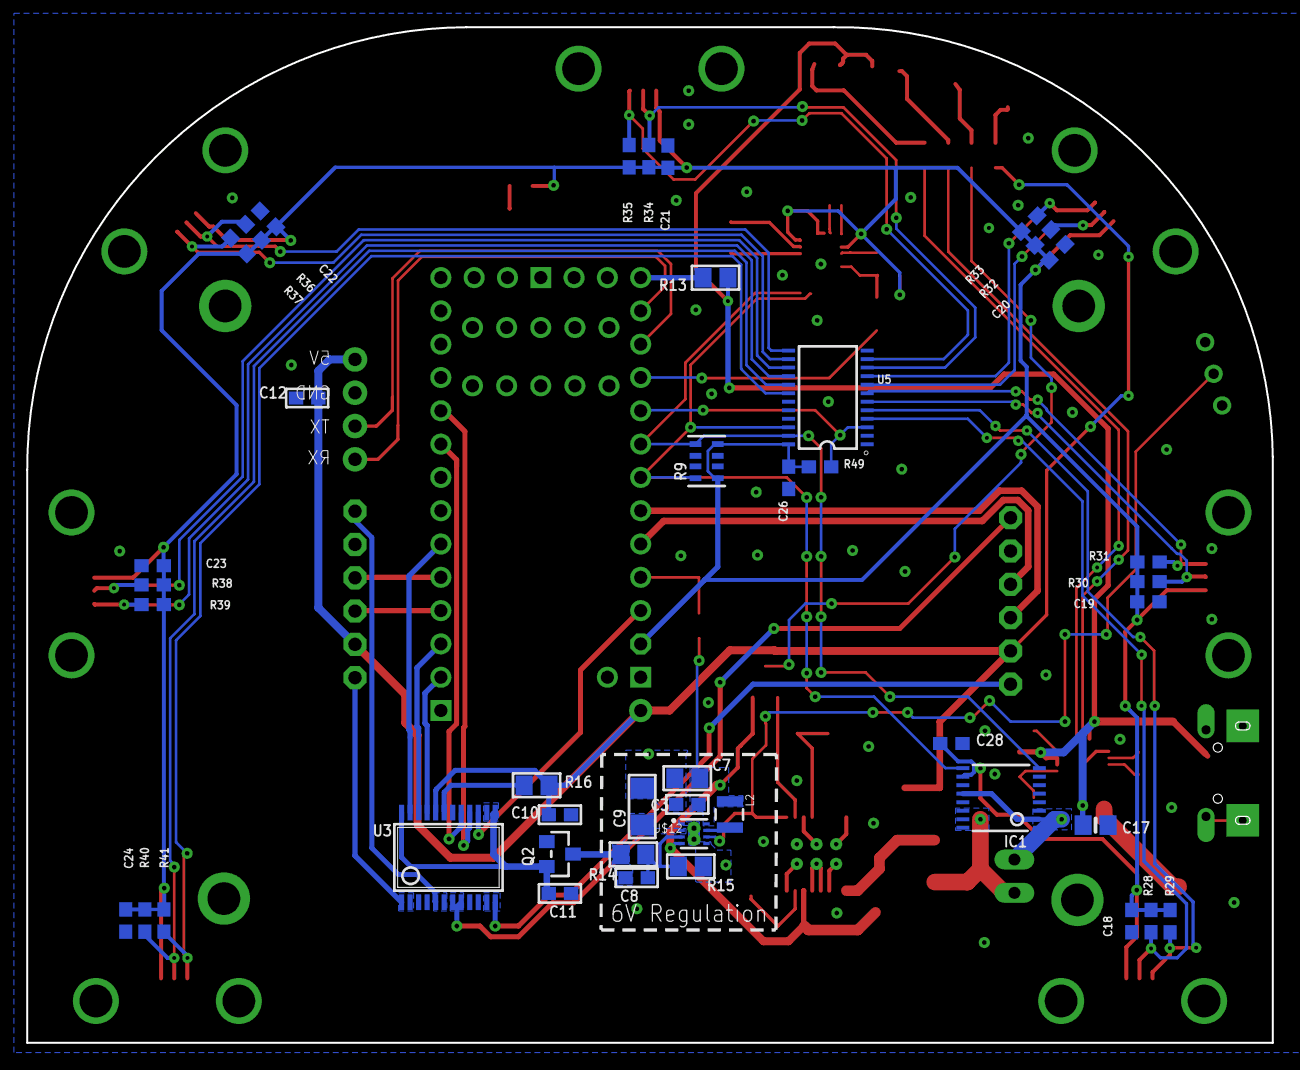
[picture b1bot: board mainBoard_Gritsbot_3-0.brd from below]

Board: 2 copper layers, 95.0 x 77.5 mm, 115 parts (43 on the bottom side), 71 nets.

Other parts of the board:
U$7, U$23, U$28, U$29: MOUNTINGHOLE_2.5_PLATED_THICK

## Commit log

2023-09-16 Initial uploads
2023-09-16 Added readme file
2023-09-24 Code clean-ups
2023-09-28 Moved design files to a separate repository. The GTernal_design_diles is a submodule of this repository.
2023-09-28 Updated docker_build.sh
2023-09-28 Fixed typo in docker_build.sh
2023-09-28 Minor updates
2023-09-28 Fixed typos
2023-09-28 Directory clean-ups
2023-10-02 Fixed a typo in README.md
2023-10-02 Updated setup file with date and time synchronization
2023-10-05 Added Robot 107
2023-10-17 Updated the design files submodule
2023-10-17 Testing docker_run.sh with local config files
2023-10-17 Merged with 'local' branch. The firmware docker image now uses local config files
2023-10-18 Updated README.md with Raspberry Pi OS version compatibility message
2023-10-18 Updated readme with Raspberry Pi OS version compatibility message
2023-10-18 Fixed typo in README.md
2023-10-25 Fixed typos in README.md
2023-10-26 Updated the automatic setup procedure
2023-10-30 Updated the automatic setup process
2023-10-31 Updated the setup scripts
2023-10-31 Updated the setup script
2023-11-01 Updated the autoatic setup process
2023-11-01 Updated README.md with the new setup process
2023-11-12 Added fast charging feature for the new PCB
2024-03-09 Updated the motor PID controller to use timer interrupts and code clean-ups
2024-03-19 Test codes upload
2024-03-19 Included watchdog library
2024-04-28 Saving the up-to-date test branch
2024-04-30 Added local installation scripts and fast charging mode for the main branch
2024-04-30 Indentation test for markdowns
2024-04-30 Indentation test for markdowns 2
2024-04-30 Indentation test for markdowns 3
2024-04-30 Edited README.md
2024-12-06 Interrupt-based motor control
2024-12-11 Initial simple changes to limit acceleration of motors and avoid voltage sag.
2024-12-11 Updated byte to uint_8 to avoid conflicts. Byte is defined as uint_8 in Arduino anyway.
2024-12-11 Updated the GTernal library to the latest interrupt-based motor controller. Included the initial simple motor accleration limit.
2024-12-11 Removed erroneous brake command.
2025-02-20 Added discover_robots.sh for an easy robot status check.
2025-02-20 Updated setup scripts for a mass production
2025-03-03 Testing new automatic setup scripts
2025-03-05 Bug fixes in setup scripts
2025-03-05 Git clone as pi user
2025-03-05 Updated the address of the local docker registry for testing
2025-03-06 Updated automatic setup scripts
2025-03-06 Updated the full setup script
2025-03-06 Fixed a typo
2025-03-06 Updated mac_list for testing
2025-03-06 Updated the ip address for testing
2025-03-06 Using scp for updating the mac_list file
2025-03-07 Updated docker files
2025-03-07 Merged Teensy firmware codes from the test branch
2025-03-07 Set the design file submodule to track main
2025-03-07 Docker cross platform build does not need QEMU in a Dockerfile anymore
2025-03-07 File clean-ups
2025-03-07 Updated docker scripts
2025-03-07 Docker script clean-up
2025-03-07 Updated readme files
2025-03-10 Updated docker scripts. Added base_image and registry directories inside the docker directory.
2025-03-10 Updated the default GTernal branch to the main
2025-03-10 Added automatic network interface selection feature for the shutdown script
2025-03-10 Updated docker scripts for building/deploying base image for the firmware
2025-03-10 Fixed typos in docker scripts
2025-03-10 Supressed the standard output for the base image setup script
2025-03-10 Fixed errors for docker push scripts
2025-03-10 Updated docker and setup scripts
2025-03-10 Updated docker_pull.sh to be executable
2025-03-10 Updated the IP address of the host
2025-03-11 Changed host ip address for testing
2025-03-12 Updated the setup scripts to account for robots with no internet access
2025-03-12 Changed the default IP address of the host for testing
2025-03-12 Changed the default IP address
2025-03-12 Updated instructions
2025-03-12 Updated the readme
2025-03-12 Updated how setup status messages are displayed for the robots
2025-03-12 Enabled INA260 and BNO55
2025-03-12 Teensy firmware code clean-up
2025-03-12 Fixed typos in readme
2025-03-13 Integrated robot discovery feature
2025-03-13 Starting IP addresses for network device discovery can be configured in env_variables.sh
2025-03-13 Added automatic network device discovery script. Updated restart_docker_containers.sh to use sshpass

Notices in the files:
parts and their libraries:
microbuilder: This work is placed in the public domain, and may be freely used for commercial and non-commercial work with the following conditions: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
SparkFun-Connectors: Licensing: Creative Commons ShareAlike 4.0 International - https://creativecommons.org/licenses/by-sa/4.0
